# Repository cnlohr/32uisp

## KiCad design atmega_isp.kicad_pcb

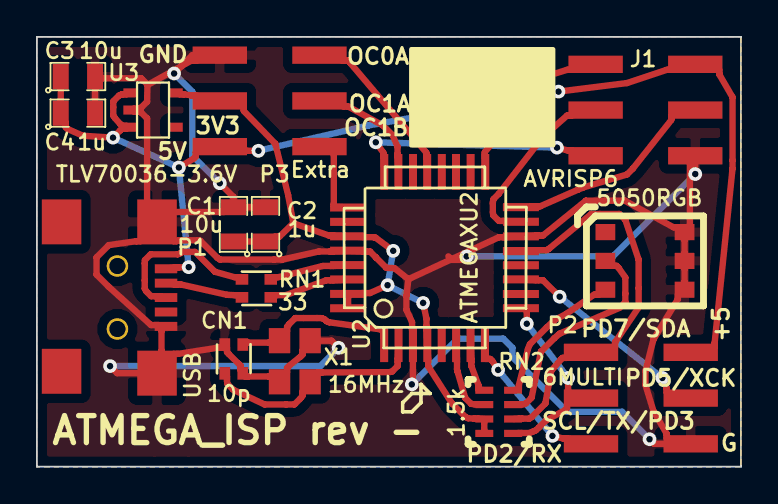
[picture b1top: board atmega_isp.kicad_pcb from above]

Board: 2 copper layers, 39.1 x 23.9 mm, 15 parts (0 on the bottom side), 24 nets.

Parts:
C1, C3: 10u; SM0805
C2, C4: 1u; SM0805
CN1: 10p; NETWORK0606
D1: 5050RGB
J1: AVRISP6; RIBBON6SMT
P1: USB; USB-MiniBBig
P2: 6MULTI; RIBBON6SMT
P3: Extra; RIBBON6SMT
RN1: 33; NETWORK0606
RN2: 1.5k; NETWORK1206
U2: ATMEGAXU2; TQFP32
U3: TLV70036-3.6V; SOT23-5
X1: 16MHz; XTAL4P

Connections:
+3.3V: C1.1, C2.1, P3.4, RN2.7, RN2.8, U2.4, U2.27, U2.31, U2.32, U3.5
+5V: C3.1, C4.1, J1.2, P1.1, P2.2, P3.2, U3.1, U3.3
/PB7/OC0A: P3.5, U2.21
/PC5/OC1B: P3.1, U2.25
/PC6/OC1A: P3.3, U2.23
/PD2/RX: P2.5, U2.8
/PD5/XCK: P2.4, U2.11
/SCL/TX/PD3: P2.3, RN2.1, U2.9
/SDA/PD7: P2.1, RN2.2, U2.13
GND: C1.2, C2.2, C3.2, C4.2, CN1.2, CN1.3, D1.4, D1.5, D1.6, J1.6, P1.5, P1.6, P1.7, P2.6, P3.6, U2.3, U2.14, U2.28, U3.2, X1.3, X1.4
unnamed: RN2.6, U2.6
unnamed: CN1.1, U2.2, X1.1
unnamed: CN1.4, U2.1, X1.2
unnamed: J1.1, U2.17
unnamed: J1.3, U2.15
unnamed: J1.4, U2.16
unnamed: D1.3, RN2.4
unnamed: D1.2, RN2.3
unnamed: RN2.5, U2.7
unnamed: J1.5, U2.24
unnamed: RN1.2, U2.29
unnamed: RN1.4, U2.30
unnamed: P1.3, RN1.1
unnamed: P1.2, RN1.3

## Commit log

2014-09-27 add design

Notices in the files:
atmega_isp.kicad_pcb:
(C) 2014 C. Lohr
